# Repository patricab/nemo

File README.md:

# Nemo - Template board for Atmega328P Microcontroller

This is a template project for a sufrace mounted board, for use with the Atmega328P TQFP package.

What's included:
- Full KiCAD project
- Bill of Materials (BOM)
- Schematic PDF Export

# Full KiCAD project
I have included all project files for use with the open source CAD software KiCAD.
This includes the schematic file, component libraries, netlist and PCB-files

# Schematic PDF Export
Included is a PDF export of the schematic file:

# Bill of Materials (BOM)
I have also added a full bill of materials (minus the header-pins), which are sourced from [LCSC](LCSC.com).

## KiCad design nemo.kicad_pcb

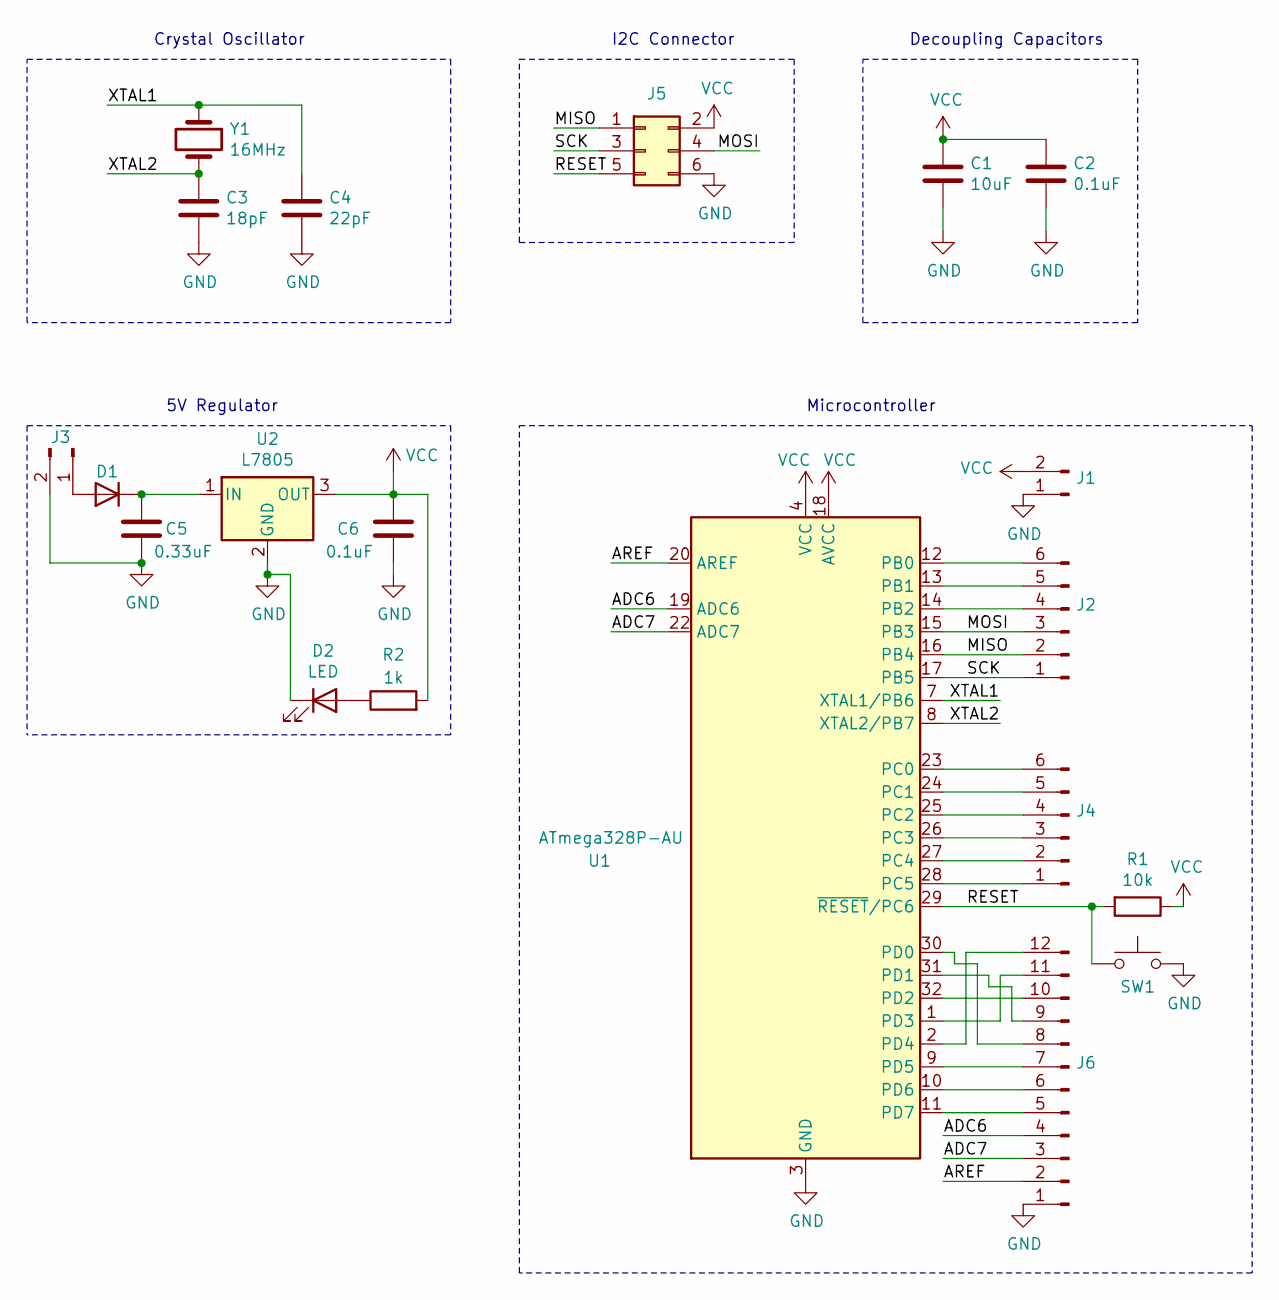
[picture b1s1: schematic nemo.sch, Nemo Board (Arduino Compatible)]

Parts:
C1: 10uF; C_0603_1608Metric_Pad1.05x0.95mm_HandSolder
C2, C6: 0.1uF; C_0603_1608Metric_Pad1.05x0.95mm_HandSolder
C3: 18pF; C_0603_1608Metric_Pad1.05x0.95mm_HandSolder
C4: 22pF; C_0603_1608Metric_Pad1.05x0.95mm_HandSolder
C5: 0.33uF; C_0603_1608Metric_Pad1.05x0.95mm_HandSolder
D1: 1N4001; D_DO-41_SOD81_P10.16mm_Horizontal
D2: LED; LED_0603_1608Metric_Pad1.05x0.95mm_HandSolder
J1, J3: Conn_01x02_Male; PinHeader_1x02_P1.27mm_Vertical
J2, J4: Conn_01x06_Male; PinHeader_1x06_P1.27mm_Vertical
J5: Conn_02x03_Odd_Even; PinHeader_2x03_P1.27mm_Vertical
J6: Conn_01x12_Male; PinHeader_1x12_P1.27mm_Vertical
R1: 10k; R_0603_1608Metric_Pad1.05x0.95mm_HandSolder
R2: 1k; R_0603_1608Metric_Pad1.05x0.95mm_HandSolder
SW1: SW_Push; SW_Push_1P1T_NO_CK_KSC7xxJ
U1: ATmega328P-AU; TQFP-32_7x7mm_P0.8mm
U2: L7805; TO-263-2
Y1: 16MHz; Crystal_SMD_3225-4Pin_3.2x2.5mm_HandSoldering

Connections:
/ADC6: J6.4, U1.19 (ADC6)
/ADC7: J6.3, U1.22 (ADC7)
/AREF: J6.2, U1.20 (AREF)
/MISO: J2.2, J5.1, U1.16 (PB4)
/MOSI: J2.3, J5.4, U1.15 (PB3)
/RESET: J5.5, R1.2, SW1.1, U1.29 (~RESET~/PC6)
/SCK: J2.1, J5.3, U1.17 (PB5)
/XTAL1: C4.2, U1.7 (XTAL1/PB6), Y1.1
/XTAL2: C3.2, U1.8 (XTAL2/PB7), Y1.2
GND: C1.2, C2.2, C3.1, C4.1, C5.2, C6.2, D2.1 (K), J1.1, J3.2, J5.6, J6.1, SW1.2, U1.3 (GND), U1.5 (GND), U1.21 (GND), U2.2 (GND)
unnamed: C5.1, D1.1 (K), U2.1 (IN)
unnamed: D1.2 (A), J3.1
unnamed: D2.2 (A), R2.1
unnamed: J2.4, U1.14 (PB2)
unnamed: J2.5, U1.13 (PB1)
unnamed: J2.6, U1.12 (PB0)
unnamed: J4.1, U1.28 (PC5)
unnamed: J4.2, U1.27 (PC4)
unnamed: J4.3, U1.26 (PC3)
unnamed: J4.4, U1.25 (PC2)
unnamed: J4.5, U1.24 (PC1)
unnamed: J4.6, U1.23 (PC0)
unnamed: J6.5, U1.11 (PD7)
unnamed: J6.6, U1.10 (PD6)
unnamed: J6.7, U1.9 (PD5)
unnamed: J6.8, U1.30 (PD0)
unnamed: J6.9, U1.31 (PD1)
unnamed: J6.10, U1.32 (PD2)
unnamed: J6.11, U1.1 (PD3)
unnamed: J6.12, U1.2 (PD4)
VCC: C1.1, C2.1, C6.1, J1.2, J5.2, R1.1, R2.2, U1.4 (VCC), U1.6 (VCC), U1.18 (AVCC), U2.3 (OUT)

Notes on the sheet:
5V Regulator
Crystal Oscillator
Decoupling Capacitors
I2C Connector
Microcontroller

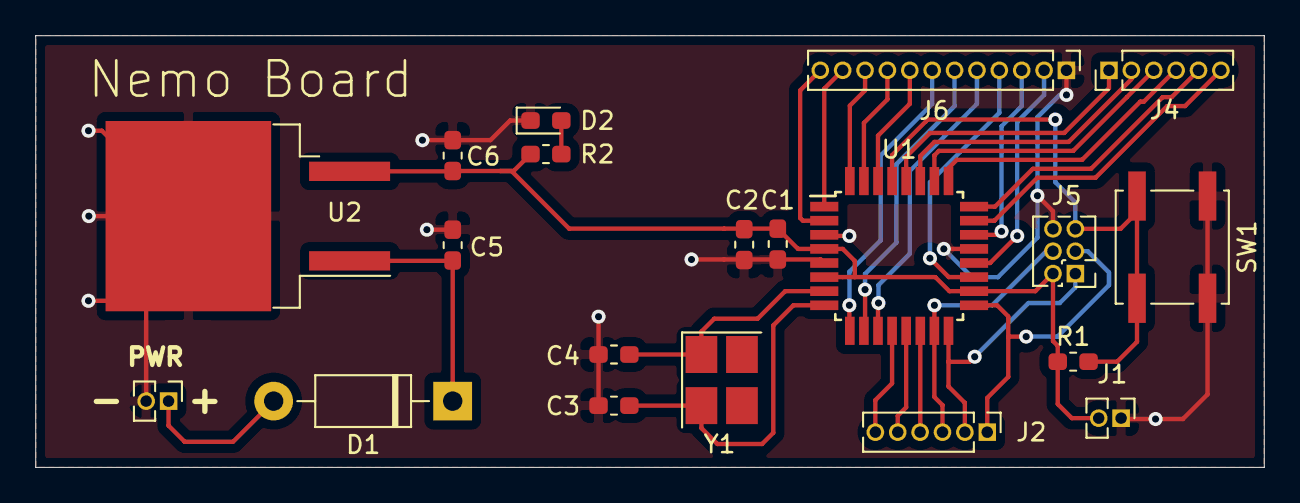
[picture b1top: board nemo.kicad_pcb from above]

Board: 2 copper layers, 69.7 x 24.5 mm, 20 parts (0 on the bottom side), 31 nets.

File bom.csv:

Reference, Value, Footprint, Datasheet,Price (USD),LCSC Part #
J5,Conn_02x03_Odd_Even,Connector_PinHeader_1.27mm:PinHeader_2x03_P1.27mm_Vertical,~,,
C5,0.33uF,Capacitor_SMD:C_0603_1608Metric_Pad1.05x0.95mm_HandSolder,~,0.015829,C507077
"C6, C2",0.1uF,Capacitor_SMD:C_0603_1608Metric_Pad1.05x0.95mm_HandSolder,~,0.015126,C282518
Y1,16MHz,Crystal:Crystal_SMD_3225-4Pin_3.2x2.5mm_HandSoldering,~,0.504318,C387370
C3,18pF,Capacitor_SMD:C_0603_1608Metric_Pad1.05x0.95mm_HandSolder,~,0.0169,C415402
C4,22pF,Capacitor_SMD:C_0603_1608Metric_Pad1.05x0.95mm_HandSolder,~,0.003915,C376775
C1,10uF,Capacitor_SMD:C_0603_1608Metric_Pad1.05x0.95mm_HandSolder,~,0.053491,C91606
D1,1N4001,Diode_THT:D_DO-41_SOD81_P10.16mm_Horizontal,http://www.vishay.com/docs/88503/1n4001.pdf,0.019891,C331627
J3,Conn_01x02_Male,Connector_PinHeader_1.27mm:PinHeader_1x02_P1.27mm_Vertical,~,,
R2,1k,Resistor_SMD:R_0603_1608Metric_Pad1.05x0.95mm_HandSolder,~,0.002629,C328340
D2,LED,LED_SMD:LED_0603_1608Metric_Pad1.05x0.95mm_HandSolder,~,0.028633,C434428
SW1,SW_Push,Button_Switch_SMD:SW_Push_1P1T_NO_CK_KSC7xxJ,~,,
J6,Conn_01x12_Male,Connector_PinHeader_1.27mm:PinHeader_1x12_P1.27mm_Vertical,~,,
U1,ATmega328P-AU,Package_QFP:TQFP-32_7x7mm_P0.8mm,http://ww1.microchip.com/downloads/en/DeviceDoc/ATmega328_P%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,2.072955,C14877
J4,Conn_01x06_Male,Connector_PinHeader_1.27mm:PinHeader_1x06_P1.27mm_Vertical,~,,
J2,Conn_01x06_Male,Connector_PinHeader_1.27mm:PinHeader_1x06_P1.27mm_Vertical,~,,
J1,Conn_01x02_Male,Connector_PinHeader_1.27mm:PinHeader_1x02_P1.27mm_Vertical,~,,
R1,10k,Resistor_SMD:R_0603_1608Metric_Pad1.05x0.95mm_HandSolder,~,0.000908,C81087
U2,L7805,Package_TO_SOT_SMD:TO-263-2,http://www.st.com/content/ccc/resource/technical/document/da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,0.375455,C53236
,,,,,
,,,Total (USD),3.11005,
,,,Total (NOK),31.1005,
,,,+moms,38.875625,

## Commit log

2020-05-22 Initial commit!
2020-05-23 * Added README.md * Added BOM - bom.csv * Exportet schematic to pdf - schematic.pdf
2020-05-26 * Changed README.md
2020-06-07 * Improved image display for schematic
